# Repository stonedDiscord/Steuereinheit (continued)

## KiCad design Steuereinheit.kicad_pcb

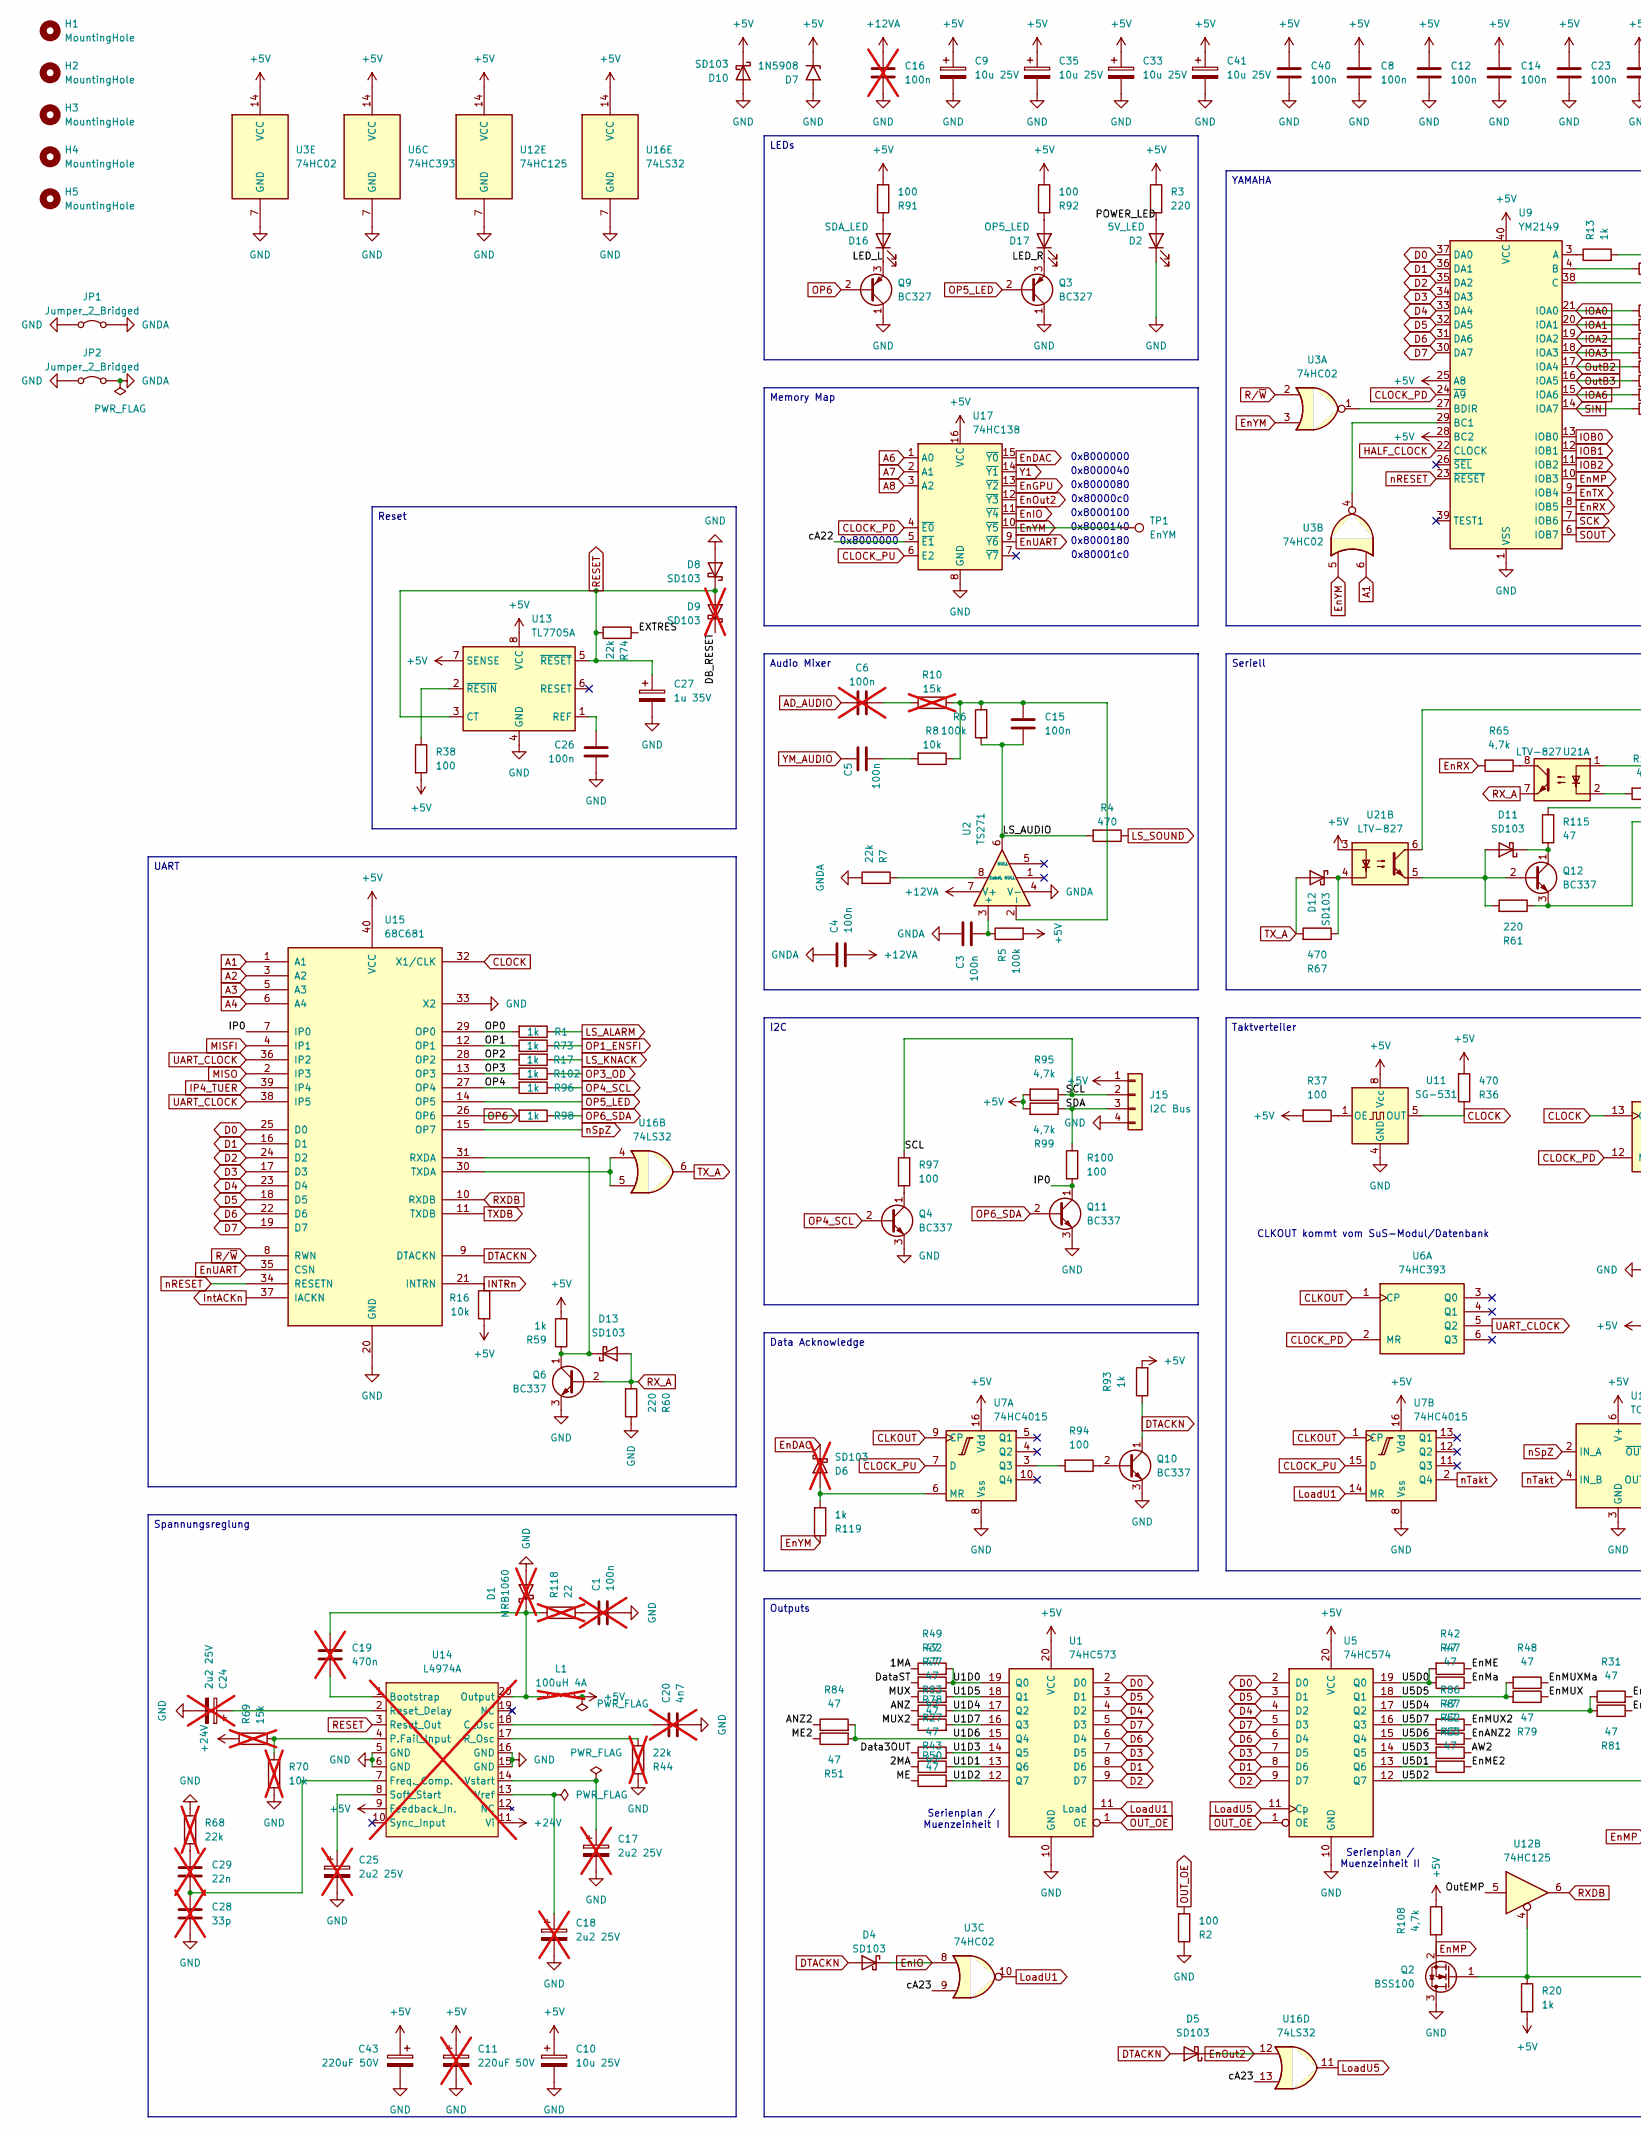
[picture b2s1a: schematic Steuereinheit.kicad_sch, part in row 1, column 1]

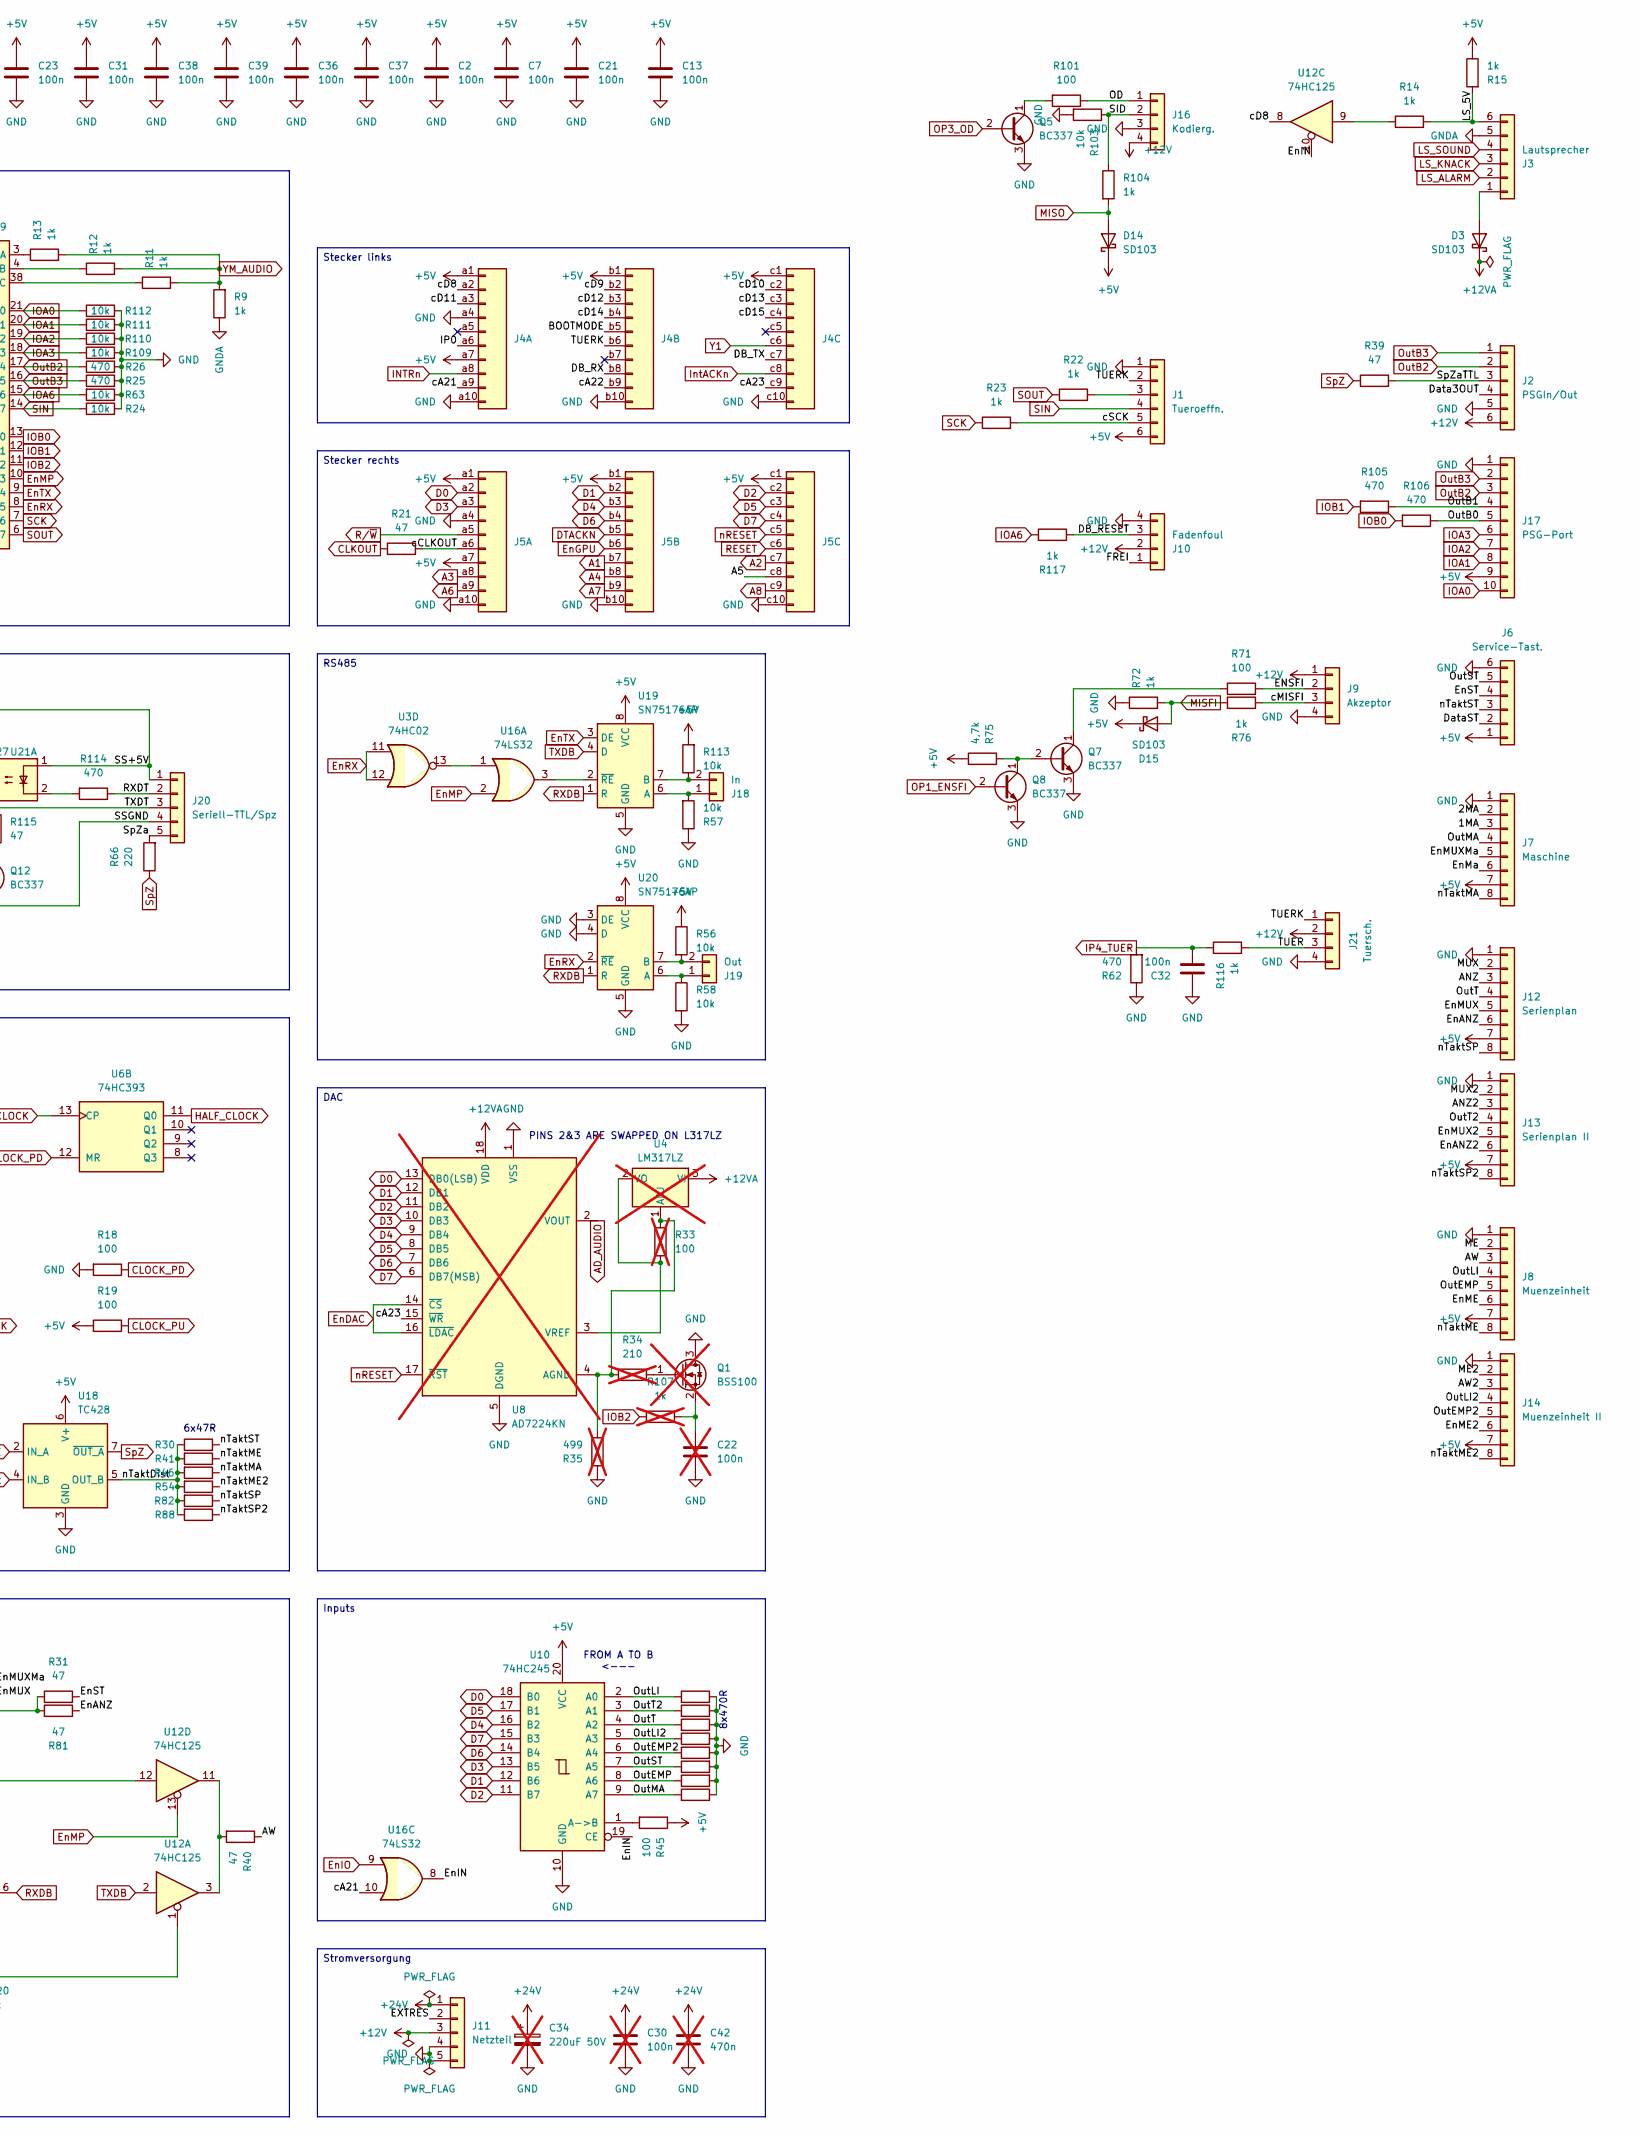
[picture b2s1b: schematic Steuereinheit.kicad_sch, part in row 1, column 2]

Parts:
C1, C6, C16, C22, C30: 100n; C_Axial_L3.8mm_D2.6mm_P7.50mm_Horizontal; not fitted
C2, C3, C4, C5, C7, C8, C12, C13, C14, C15, C21, C23, C26, C31, C32, C36, C37, C38, C39, C40: 100n; C_Axial_L3.8mm_D2.6mm_P7.50mm_Horizontal
C9, C10, C33, C35, C41: 10u 25V; CP_Radial_Tantal_D4.5mm_P2.50mm
C11, C34: 220uF 50V; CP_Radial_D12.5mm_P5.00mm; not fitted
C17, C18, C24, C25: 2u2 25V; CP_Radial_Tantal_D4.5mm_P2.50mm; not fitted
C19, C42: 470n; C_Rect_L9.0mm_W2.5mm_P7.50mm_MKT; not fitted
C20: 4n7; C_Rect_L7.0mm_W2.0mm_P5.00mm; not fitted
C27: 1u 35V; CP_Radial_Tantal_D4.5mm_P2.50mm
C28: 33p; C_Disc_D3.0mm_W1.6mm_P2.50mm; not fitted
C29: 22n; C_Rect_L7.0mm_W2.0mm_P5.00mm; not fitted
C43: 220uF 50V; CP_Radial_D12.5mm_P5.00mm
D1: MRB1060; TO-220-2_Vertical; not fitted
D2: 5V_LED; LED_D5.0mm
D3, D4, D5, D8, D10, D11, D12, D13, D14, D15: SD103; D_DO-35_SOD27_P7.62mm_Horizontal
D6, D9: SD103; D_DO-35_SOD27_P7.62mm_Horizontal; not fitted
D7: 1N5908; D_DO-201AE_P15.24mm_Horizontal
D16: SDA_LED; LED_D5.0mm
D17: OP5_LED; LED_D5.0mm
H1, H2, H3, H4, H5: MountingHole; MountingHole_4.3mm_M4
J1: Tueroeffn.; PinHeader_1x06_P2.54mm_Vertical
J2: PSGIn/Out; PinHeader_1x06_P2.54mm_Vertical
J3: Lautsprecher; PinHeader_1x06_P2.54mm_Vertical
J4, J5: DIN41612_03x10_ABC
J6: Service-Tast.; PinHeader_1x06_P2.54mm_Vertical
J7: Maschine; PinHeader_1x08_P2.54mm_Vertical
J8: Muenzeinheit; PinHeader_1x08_P2.54mm_Vertical
J9: Akzeptor; PinHeader_1x04_P2.54mm_Vertical
J10: Fadenfoul; PinHeader_1x04_P2.54mm_Vertical
J11: Netzteil; PinHeader_1x05_P2.54mm_Vertical
J12: Serienplan; PinHeader_1x08_P2.54mm_Vertical
J13: Serienplan II; PinHeader_1x08_P2.54mm_Vertical
J14: Muenzeinheit II; PinHeader_1x08_P2.54mm_Vertical
J15: I2C Bus; PinHeader_1x04_P2.54mm_Vertical
J16: Kodierg.; PinHeader_1x04_P2.54mm_Vertical
J17: PSG-Port; PinHeader_1x10_P2.54mm_Vertical
J18: In; PinHeader_1x02_P2.54mm_Vertical
J19: Out; PinHeader_1x02_P2.54mm_Vertical
J20: Seriell-TTL/Spz; PinHeader_1x05_P2.54mm_Vertical
J21: Tuersch.; PinHeader_1x04_P2.54mm_Vertical
JP1, JP2: Jumper_2_Bridged; SolderJumper-2_P1.3mm_Bridged_Pad1.0x1.5mm
L1: 100uH 4A; L_Toroid_Vertical_L24.6mm_W15.5mm_P11.44mm_Pulse_KM-4; not fitted
Q1: BSS100; TO-92; not fitted
Q2: BSS100; TO-92
Q3, Q9: BC327; TO-92
Q4, Q5, Q6, Q7, Q8, Q10, Q11, Q12: BC337; TO-92
R1, R9, R11, R12, R13, R14, R15, R17, R20, R22, R23, R59, R72, R73, R76, R93, R96, R98, R102, R104, R116, R117, R119: 1k; R_Axial_DIN0207_L6.3mm_D2.5mm_P10.16mm_Horizontal
R2, R18, R19, R37, R38, R45, R71, R91, R92, R94, R97, R100, R101: 100; R_Axial_DIN0207_L6.3mm_D2.5mm_P10.16mm_Horizontal
R3, R60, R61, R66: 220; R_Axial_DIN0207_L6.3mm_D2.5mm_P10.16mm_Horizontal
R4, R25, R26, R28, R29, R36, R55, R62, R64, R67, R80, R85, R89, R90, R105, R106, R114: 470; R_Axial_DIN0207_L6.3mm_D2.5mm_P10.16mm_Horizontal
R5, R6: 100k; R_Axial_DIN0207_L6.3mm_D2.5mm_P10.16mm_Horizontal
R7, R74: 22k; R_Axial_DIN0207_L6.3mm_D2.5mm_P10.16mm_Horizontal
R8, R16, R24, R56, R57, R58, R63, R103, R109, R110, R111, R112, R113: 10k; R_Axial_DIN0207_L6.3mm_D2.5mm_P10.16mm_Horizontal
R10, R69: 15k; R_Axial_DIN0207_L6.3mm_D2.5mm_P10.16mm_Horizontal; not fitted
R21, R27, R30, R31, R32, R39, R40, R41, R42, R43, R46, R47, R48, R49, R50, R51, R52, R53, R54, R77, R78, R79, R81, R82, R83, R84, R86, R87, R88, R115: 47; R_Axial_DIN0207_L6.3mm_D2.5mm_P10.16mm_Horizontal
R33: 100; R_Axial_DIN0207_L6.3mm_D2.5mm_P10.16mm_Horizontal; not fitted
R34: 210; R_Axial_DIN0207_L6.3mm_D2.5mm_P10.16mm_Horizontal; not fitted
R35: 499; R_Axial_DIN0207_L6.3mm_D2.5mm_P10.16mm_Horizontal; not fitted
R44, R68: 22k; R_Axial_DIN0207_L6.3mm_D2.5mm_P10.16mm_Horizontal; not fitted
R65, R75, R95, R99, R108: 4,7k; R_Axial_DIN0207_L6.3mm_D2.5mm_P10.16mm_Horizontal
R70: 10k; R_Axial_DIN0207_L6.3mm_D2.5mm_P10.16mm_Horizontal; not fitted
R107: 1k; R_Axial_DIN0207_L6.3mm_D2.5mm_P10.16mm_Horizontal; not fitted
R118: 22; R_Axial_DIN0207_L6.3mm_D2.5mm_P10.16mm_Horizontal; not fitted
TP1: EnYM; TestPoint_Pad_D1.0mm
U1: 74HC573; DIP-20_W7.62mm
U2: TS271; DIP-8_W7.62mm
U3: 74HC02; DIP-14_W7.62mm
U4: LM317LZ; TO-92; not fitted
U5: 74HC574; DIP-20_W7.62mm
U6: 74HC393; DIP-14_W7.62mm
U7: 74HC4015; DIP-16_W7.62mm
U8: AD7224KN; DIP-18_W7.62mm; not fitted
U9: YM2149; DIP-40_W15.24mm
U10: 74HC245; DIP-20_W7.62mm
U11: SG-531; Oscillator_SeikoEpson_SG-8002DC
U12: 74HC125; DIP-14_W7.62mm
U13: TL7705A; DIP-8_W7.62mm
U14: L4974A; DIP-20_W7.62mm; not fitted
U15: 68C681; DIP-40_W15.24mm
U16: 74LS32; DIP-14_W7.62mm
U17: 74HC138; DIP-16_W7.62mm
U18: TC428; DIP-8_W7.62mm
U19, U20: SN75176AP; DIP-8_W7.62mm
U21: LTV-827; DIP-8_W7.62mm

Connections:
+5V: C2.2, C7.2, C8.1, C9.1, C10.1, C11.1, C12.1, C13.1, C14.1, C21.1, C23.1, C31.1, C33.1, C35.1, C36.1, C37.1, C38.1, C39.1, C40.1, C41.1, C43.1, D7.1 (A1), D10.1 (K), D14.1 (K), D15.1 (K), J1.6, J4.a1, J4.a7, J4.b1, J4.c1, J5.a1, J5.a7, J5.b1, J5.c1, J6.1, J7.7, J8.7, J12.7, J13.7, J14.7, J15.1, J17.9, L1.2, R3.1, R5.2, R15.1, R16.2, R19.2, R20.2, R36.2, R37.2, R38.2, R45.1, R56.1, R59.2, R75.2, R91.2, R92.2, R93.2, R95.2, R99.2, R108.1, R113.2, U1.20 (VCC), U3.14 (VCC), U5.20 (VCC), U6.14 (VCC), U7.16 (Vdd), U9.25 (A8), U9.28 (BC2), U9.40 (VCC), U10.20 (VCC), U11.8 (Vcc), U12.14 (VCC), U13.7 (SENSE), U13.8 (VCC), U14.9 (Feedback_In.), U15.40 (VCC), U16.14 (VCC), U17.16 (VCC), U18.6 (V+), U19.8 (VCC), U20.8 (VCC), U21.3
+12V: J2.6, J9.1, J10.2, J11.3, J16.4, J21.2
+12VA: C4.2, C16.1, D3.1 (K), U2.7 (V+), U4.3 (VI), U8.18 (VDD)
+24V: C30.1, C34.1, C42.2, J11.1, R69.1, U14.11 (Vi)
/1MA: J7.3, R49.1
/2MA: J7.2, R50.1
/A5: J5.c8
/ANZ: J12.3, R78.1
/ANZ2: J13.3, R84.1
/AW: J8.3, R40.1
/AW2: J14.3, R52.1
/BOOTMODE: J4.b5
/DB_RESET: D9.1 (K), J10.3, R117.1
/DB_RX: J4.b8
/DB_TX: J4.c7
/Data3OUT: J2.4, R27.1
/DataST: J6.2, R32.2
/ENSFI: J9.2, R71.2
/EXTRES: J11.2, R74.1
/EnANZ: J12.6, R81.1
/EnANZ2: J13.6, R87.1
/EnIN: U10.19 (CE), U12.10, U16.8
/EnME: J8.6, R42.1
/EnME2: J14.6, R53.1
/EnMUX: J12.5, R79.1
/EnMUX2: J13.5, R86.1
/EnMUXMa: J7.5, R48.1
/EnMa: J7.6, R47.1
/EnST: J6.4, R31.2
/FREI: J10.1
/IP0: J4.a6, Q11.1 (C), R100.2, U15.7 (IP0)
/LED_L: D16.1 (K), Q9.3 (E)
/LED_R: D17.1 (K), Q3.3 (E)
/LS_5V: J3.6, R14.2, R15.2
/LS_AUDIO: C15.2, R4.2, R6.2, U2.6
/ME: J8.2, R43.1
/ME2: J14.2, R51.1
/MUX: J12.2, R77.1
/MUX2: J13.2, R83.1
/OD: J16.1, R101.1
/OP0: R1.2, U15.29 (OP0)
/OP1: R73.2, U15.12 (OP1)
/OP2: R17.1, U15.28 (OP2)
/OP3: R102.2, U15.13 (OP3)
/OP4: R96.2, U15.27 (OP4)
/OutB0: J17.5, R106.1
/OutB1: J17.4, R105.1
/OutEMP: J8.5, R29.1, U10.8 (A6), U12.5
/OutEMP2: J14.5, R90.1, U10.6 (A4)
/OutLI: J8.4, R64.2, U10.2 (A0)
/OutLI2: J14.4, R89.1, U10.5 (A3)
/OutMA: J7.4, R55.2, U10.9 (A7)
/OutST: J6.5, R28.1, U10.7 (A5)
/OutT: J12.4, R80.2, U10.4 (A2)
/OutT2: J13.4, R85.2, U10.3 (A1)
/POWER_LED: D2.2 (A), R3.2
/RXDT: J20.2, R114.1
/SCL: J15.2, R95.1, R97.1
/SDA: J15.3, R99.1, R100.1
/SID: J16.2, R103.1, R104.1
/SS+5V: J20.1, U21.1, U21.6
/SSGND: J20.4, Q12.3 (E), R61.1
/SpZa: J20.5, R66.2
/SpZaTTL: J2.3, R39.2
/TUER: J21.3, R116.1
/TUERK: J1.2, J4.b6, J21.1
/TXDT: J20.3, R115.1
/U1D0: R32.1, R49.2, U1.19 (Q0)
/U1D1: R50.2, U1.13 (Q6)
/U1D2: R43.2, U1.12 (Q7)
/U1D3: R27.2, U1.14 (Q5)
/U1D4: R78.2, U1.17 (Q2)
/U1D5: R77.2, U1.18 (Q1)
/U1D6: R51.2, R84.2, U1.15 (Q4)
/U1D7: R83.2, U1.16 (Q3)
/U5D0: R42.2, R47.2, U5.19 (Q0)
/U5D1: R53.2, U5.13 (Q6)
/U5D2: U5.12 (Q7), U12.12
/U5D3: R52.2, U5.14 (Q5)
/U5D4: R31.1, R81.2, U5.17 (Q2)
/U5D5: R48.2, R79.2, U5.18 (Q1)
/U5D6: R87.2, U5.15 (Q4)
/U5D7: R86.2, U5.16 (Q3)
/cA21: J4.a9, U16.10
/cA22: J4.b9, U17.5 (~E1)
/cA23: J4.c9, U3.9, U8.15 (~WR), U16.13
/cCLKOUT: J5.a6, R21.2
/cD8: J4.a2, U12.8
/cD9: J4.b2
/cD10: J4.c2
/cD11: J4.a3
/cD12: J4.b3
/cD13: J4.c3
/cD14: J4.b4
/cD15: J4.c4
/cMISFI: J9.3, R76.1
/cSCK: J1.5, R23.2
/nTaktDist: R30.1, R41.2, R46.2, R54.2, R82.2, R88.2, U18.5 (OUT_B)
/nTaktMA: J7.8, R46.1
/nTaktME: J8.8, R41.1
/nTaktME2: J14.8, R54.1
/nTaktSP: J12.8, R82.1
/nTaktSP2: J13.8, R88.1
/nTaktST: J6.3, R30.2
A1: J5.b7, U3.6, U15.1 (A1)
A2: J5.c7, U15.3 (A2)
A3: J5.a8, U15.5 (A3)
A4: J5.b8, U15.6 (A4)
A6: J5.a9, U17.1 (A0)
A7: J5.b9, U17.2 (A1)
A8: J5.c9, U17.3 (A2)
AD_AUDIO: C6.1, U8.2 (VOUT)
CLKOUT: R21.1, U6.1 (CP), U7.1 (CP), U7.9 (CP)
CLOCK: R36.1, U6.13 (CP), U11.5 (OUT), U15.32 (X1/CLK)
CLOCK_PD: R18.1, U6.2 (MR), U6.12 (MR), U9.24 (~A9), U17.4 (~E0)
CLOCK_PU: R19.1, U7.7 (D), U7.15 (D), U17.6 (E2)
D0: J5.a2, U1.2 (D0), U5.2 (D0), U8.13 (DB0(LSB)), U9.37 (DA0), U10.18 (B0), U15.25 (D0)
D1: J5.b2, U1.8 (D6), U5.8 (D6), U8.12 (DB1), U9.36 (DA1), U10.12 (B6), U15.16 (D1)
D2: J5.c2, U1.9 (D7), U5.9 (D7), U8.11 (DB2), U9.35 (DA2), U10.11 (B7), U15.24 (D2)
D3: J5.a3, U1.7 (D5), U5.7 (D5), U8.10 (DB3), U9.34 (DA3), U10.13 (B5), U15.17 (D3)
D4: J5.b3, U1.4 (D2), U5.4 (D2), U8.9 (DB4), U9.33 (DA4), U10.16 (B2), U15.23 (D4)
D5: J5.c3, U1.3 (D1), U5.3 (D1), U8.8 (DB5), U9.32 (DA5), U10.17 (B1), U15.18 (D5)
D6: J5.b4, U1.6 (D4), U5.6 (D4), U8.7 (DB6), U9.31 (DA6), U10.14 (B4), U15.22 (D6)
D7: J5.c4, U1.5 (D3), U5.5 (D3), U8.6 (DB7(MSB)), U9.30 (DA7), U10.15 (B3), U15.19 (D7)
DTACKN: D4.2 (A), D5.2 (A), J5.b5, Q10.1 (C), R93.1, U15.9 (DTACKN)
EnDAC: D6.1 (K), U8.14 (~CS), U8.16 (~LDAC), U17.15 (~Y0)
EnGPU: J5.b6, U17.13 (~Y2)
EnIO: D4.1 (K), U3.8, U16.9, U17.11 (~Y4)
EnMP: Q2.2 (S), R108.2, U9.10 (IOB3), U12.13, U16.2
EnOut2: D5.1 (K), U16.12, U17.12 (~Y3)
EnRX: R65.2, U3.11, U3.12, U9.8 (IOB5), U20.2 (~RE)
EnTX: U9.9 (IOB4), U19.3 (DE)
EnUART: U15.35 (CSN), U17.9 (~Y6)
EnYM: R119.1, TP1.1, U3.3, U3.5, U17.10 (~Y5)
GND: C1.2, C2.1, C7.1, C8.2, C9.2, C10.2, C11.2, C12.2, C13.2, C14.2, C16.2, C17.2, C18.2, C20.1, C21.2, C22.2, C23.2, C24.2, C25.2, C26.2, C27.2, C28.2, C30.2, C31.2, C32.1, C33.2, C34.2, C35.2, C36.2, C37.2, C38.2, C39.2, C40.2, C41.2, C42.1, C43.2, D1.2 (A), D2.1 (K), D7.2 (A2), D8.2 (A), D10.2 (A), J1.1, J2.5, J4.a4, J4.a10, J4.b10, J4.c10, J5.a4, J5.a10, J5.b10, J5.c10, J6.6, J7.1, J8.1, J9.4, J10.4, J11.4, J11.5, J12.1, J13.1, J14.1, J15.4, J16.3, J17.1, J21.4, JP1.1 (A), JP2.1 (A), Q1.3 (D), Q2.3 (D), Q3.1 (C), Q4.3 (E), Q5.3 (E), Q6.3 (E), Q7.3 (E), Q8.3 (E), Q9.1 (C), Q10.3 (E), Q11.3 (E), R2.1, R18.2, R24.2, R25.2, R26.2, R28.2, R29.2, R35.1, R44.1, R55.1, R57.1, R58.2, R60.1, R62.1, R63.1, R64.1, R68.1, R70.1, R72.1, R80.1, R85.1, R89.2, R90.2, R103.2, R109.2, R110.2, R111.2, R112.2, U1.10 (GND), U3.7 (GND), U5.10 (GND), U6.7 (GND), U7.8 (Vss), U8.1 (VSS), U8.5 (DGND), U9.1 (VSS), U10.10 (GND), U11.4 (GND), U12.7 (GND), U13.4 (GND), U14.5 (GND), U14.6 (GND), U14.15 (GND), U14.16 (GND), U15.20 (GND), U15.33 (X2), U16.7 (GND), U17.8 (GND), U18.3 (GND), U19.5 (GND), U20.3 (DE), U20.4 (D), U20.5 (GND)
GNDA: C3.2, C4.1, J3.5, JP1.2 (B), JP2.2 (B), R7.2, R9.1, U2.4 (V-)
HALF_CLOCK: U6.11 (Q0), U9.22 (CLOCK)
INTRN: J4.a8, R16.1, U15.21 (INTRN)
IOA0: J17.10, R112.1, U9.21 (IOA0)
IOA1: J17.8, R111.1, U9.20 (IOA1)
IOA2: J17.7, R110.1, U9.19 (IOA2)
IOA3: J17.6, R109.1, U9.18 (IOA3)
IOA6: R63.2, R117.2, U9.15 (IOA6)
IOB0: R106.2, U9.13 (IOB0)
IOB1: R105.2, U9.12 (IOB1)
IOB2: R107.2, U9.11 (IOB2)
IP4_TUER: C32.2, R62.2, R116.2, U15.39 (IP4)
IntACKn: J4.c8, U15.37 (IACKN)
LS_ALARM: J3.2, R1.1
LS_KNACK: J3.3, R17.2
LS_SOUND: J3.4, R4.1
LoadU1: U1.11 (Load), U3.10, U7.14 (MR)
LoadU5: U5.11 (Cp), U16.11
MISFI: D15.2 (A), R72.2, R76.2, U15.4 (IP1)
MISO: D14.2 (A), R104.2, U15.2 (IP3)
unnamed: C1.1, R118.1
unnamed: C5.2, R8.2
unnamed: C6.2, R10.2
unnamed: C29.1, R68.2
unnamed: C19.2, D1.1 (K), L1.1, R118.2, U14.20 (Output)
unnamed: D3.2 (A), J3.1
unnamed: D6.2 (A), R119.2, U7.6 (MR)
unnamed: D11.2 (A), Q12.2 (B), R61.2, U21.5
unnamed: D11.1 (K), Q12.1 (C), R115.2
unnamed: D12.1 (K), R67.1, U21.4
unnamed: D13.1 (K), Q6.1 (C), R59.1, U15.31 (RXDA)
unnamed: D16.2 (A), R91.1
unnamed: D17.2 (A), R92.1
unnamed: J1.3, R22.2
unnamed: J18.1, R57.2, U19.6 (A)
unnamed: J18.2, R113.1, U19.7 (B)
unnamed: J19.1, R58.1, U20.6 (A)
unnamed: J19.2, R56.2, U20.7 (B)
unnamed: Q1.1 (G), R34.1
unnamed: C22.1, Q1.2 (S), R107.1
unnamed: Q2.1 (G), R20.1, U12.1, U12.4
unnamed: Q4.1 (C), R97.2
unnamed: Q5.1 (C), R101.2
unnamed: Q7.2 (B), Q8.1 (C), R75.1
unnamed: Q7.1 (C), R71.1
unnamed: Q10.2 (B), R94.1
unnamed: R14.1, U12.9
unnamed: R40.2, U12.3, U12.11
unnamed: R65.1, U21.8
unnamed: R114.2, U21.2
unnamed: C3.1, R5.1, U2.3 (+)
unnamed: C15.1, R6.1, R8.1, R10.1, U2.2 (-)
unnamed: R7.1, U2.8 (Subst.)
unnamed: R33.2, R34.2, R35.2, U4.1 (ADJ), U8.4 (AGND)
unnamed: R33.1, U4.2 (VO), U8.3 (VREF)
unnamed: R94.2, U7.3 (Q3)
unnamed: R13.1, U9.3 (A)
unnamed: R12.1, U9.4 (B)
unnamed: U3.4, U9.29 (BC1)
unnamed: U3.1, U9.27 (BDIR)
unnamed: R11.1, U9.38 (C)
unnamed: R45.2, U10.1 (A->B)
unnamed: R37.1, U11.1 (OE)
unnamed: C26.1, U13.1 (REF)
unnamed: R38.1, U13.2 (~RESIN)
unnamed: C19.1, U14.1 (Bootstrap)
unnamed: C20.2, U14.18 (C_Osc)
unnamed: C28.1, C29.2, U14.7 (Freq._Comp.)
unnamed: R69.2, R70.2, U14.4 (P.Fail_Input)
unnamed: R44.2, U14.17 (R_Osc)
unnamed: C24.1, U14.2 (Reset_Delay)
unnamed: C25.1, U14.8 (Soft_Start)
unnamed: C18.1, U14.13 (Vref)
unnamed: C17.1, U14.14 (Vstart)
unnamed: U15.30 (TXDA), U16.4, U16.5
unnamed: U3.13, U16.1
unnamed: U16.3, U19.2 (~RE)
OP1_ENSFI: Q8.2 (B), R73.1
OP3_OD: Q5.2 (B), R102.1
OP4_SCL: Q4.2 (B), R96.1
OP5_LED: Q3.2 (B), U15.14 (OP5)
OP6: Q9.2 (B), R98.2, U15.26 (OP6)
OP6_SDA: Q11.2 (B), R98.1
OUT_OE: R2.2, U1.1 (OE), U5.1 (OE)
OutB2: J2.2, J17.3, R26.1, U9.17 (IOA4)
OutB3: J2.1, J17.2, R25.1, U9.16 (IOA5)
RESET: C27.1, D8.1 (K), D9.2 (A), J5.c6, R74.2, U13.3 (CT), U13.5 (~RESET), U14.3 (Reset_Out)
RXDB: U12.6, U15.10 (RXDB), U19.1 (R), U20.1 (R)
RX_A: D13.2 (A), Q6.2 (B), R60.2, U21.7
R/~W: J5.a5, U3.2, U15.8 (RWN)
SCK: R23.1, U9.7 (IOB6)
SIN: J1.4, R24.1, U9.14 (IOA7)
SOUT: R22.1, U9.6 (IOB7)
SpZ: R39.1, R66.1, U18.7 (~OUT_A)
TXDB: U12.2, U15.11 (TXDB), U19.4 (D)
TX_A: D12.2 (A), R67.2, U16.6
UART_CLOCK: U6.5 (Q2), U15.36 (IP2), U15.38 (IP5)
Y1: J4.c6, U17.14 (~Y1)
YM_AUDIO: C5.1, R9.2, R11.2, R12.2, R13.2
nRESET: J5.c5, U8.17 (~RST), U9.23 (~RESET), U15.34 (RESETN)
nSpZ: U15.15 (OP7), U18.2 (IN_A)
nTakt: U7.2 (Q4), U18.4 (IN_B)

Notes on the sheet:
0x8000100
Serienplan / Muenzeinheit II
0x8000180
PINS 2&3 ARE SWAPPED ON L317LZ
6x47R
0x8000000
8x470R
Serienplan / Muenzeinheit I
0x8000080
0x80001c0
0x8000140
0x8000040
FROM A TO B <---
0x80000c0
CLKOUT kommt vom SuS-Modul/Datenbank
Seriell
UART
DAC
I2C
Stecker links
LEDs
Inputs
Audio Mixer
Memory Map
Taktverteiler
Stromversorgung
RS485
Stecker rechts
Outputs
Data Acknowledge
Reset
YAMAHA
Spannungsreglung

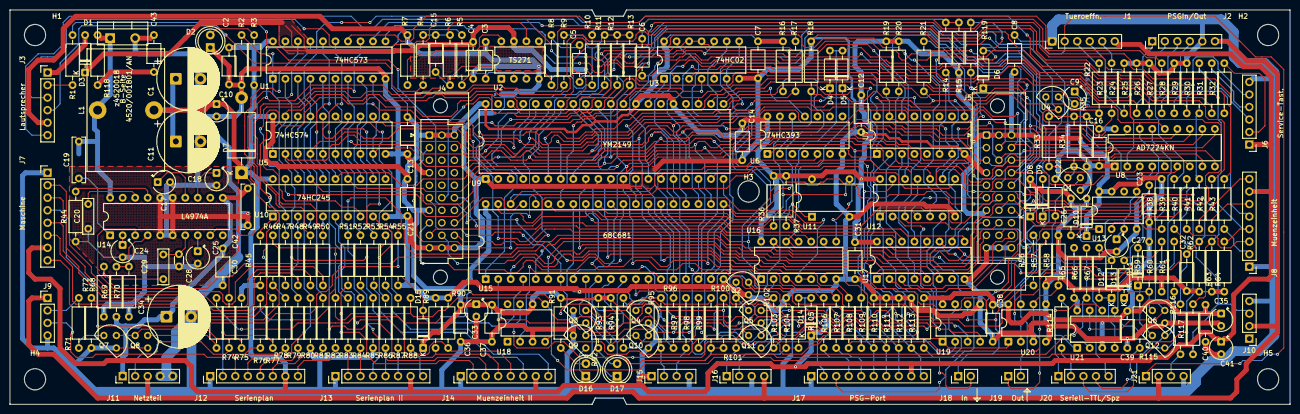
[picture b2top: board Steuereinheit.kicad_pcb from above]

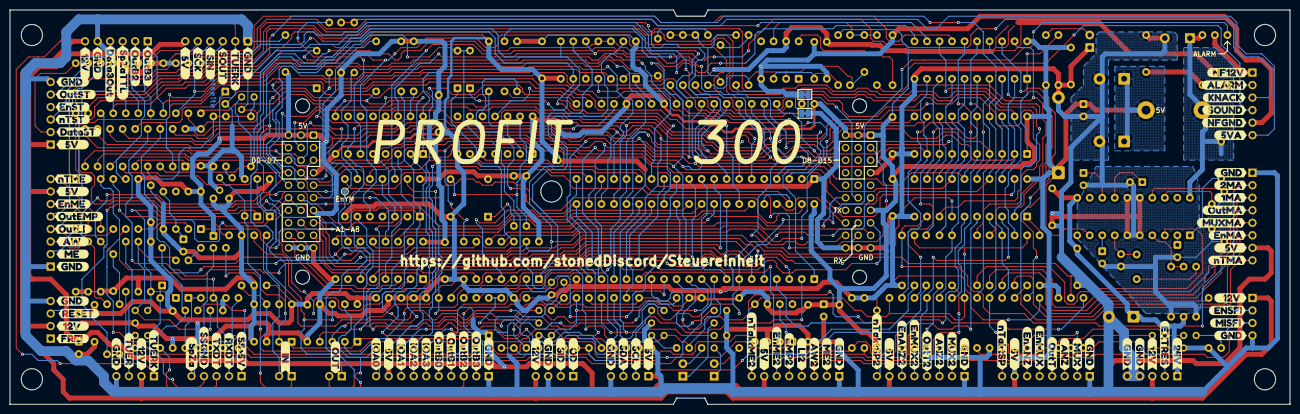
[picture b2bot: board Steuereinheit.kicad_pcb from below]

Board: 2 copper layers, 259.7 x 80.0 mm, 348 parts (109 on the bottom side), 225 nets.

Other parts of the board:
kibuzzard-6872A0A4: G***; kibuzzard-6872A0A4
kibuzzard-6872A0AF: G***; kibuzzard-6872A0AF
kibuzzard-6872A0B8: G***; kibuzzard-6872A0B8
kibuzzard-6872A0D0: G***; kibuzzard-6872A0D0
kibuzzard-6872A1B2: G***; kibuzzard-6872A1B2
kibuzzard-6872A1BE: G***; kibuzzard-6872A1BE
kibuzzard-6872A1D7: G***; kibuzzard-6872A1D7
kibuzzard-6872A1DE: G***; kibuzzard-6872A1DE
kibuzzard-6872A1E6: G***; kibuzzard-6872A1E6
kibuzzard-6872A1ED: G***; kibuzzard-6872A1ED
kibuzzard-6872A1F5: G***; kibuzzard-6872A1F5
kibuzzard-6872A2D1: G***; kibuzzard-6872A2D1
kibuzzard-6872A3BA: G***; kibuzzard-6872A3BA
kibuzzard-6872A3CC: G***; kibuzzard-6872A3CC
kibuzzard-6872A4A7: G***; kibuzzard-6872A4A7
kibuzzard-6872A4B2: G***; kibuzzard-6872A4B2
kibuzzard-6872A4BB: G***; kibuzzard-6872A4BB
kibuzzard-6872A4C0: G***; kibuzzard-6872A4C0
kibuzzard-6872A4C7: G***; kibuzzard-6872A4C7
kibuzzard-6872A4D0: G***; kibuzzard-6872A4D0
kibuzzard-6872A4D7: G***; kibuzzard-6872A4D7
kibuzzard-6872A04E: G***; kibuzzard-6872A04E
kibuzzard-6872A4E7, kibuzzard-6872A4E7#2: G***; kibuzzard-6872A4E7
kibuzzard-6872A4F2: G***; kibuzzard-6872A4F2
kibuzzard-6872A4FD: G***; kibuzzard-6872A4FD
kibuzzard-6872A5D0: G***; kibuzzard-6872A5D0
kibuzzard-6872A5D9: G***; kibuzzard-6872A5D9
kibuzzard-6872A5E5: G***; kibuzzard-6872A5E5
kibuzzard-6872A06E: G***; kibuzzard-6872A06E
kibuzzard-6872A12C: G***; kibuzzard-6872A12C
kibuzzard-6872A15D: G***; kibuzzard-6872A15D
kibuzzard-6872A18D: G***; kibuzzard-6872A18D
kibuzzard-6872A19B: G***; kibuzzard-6872A19B
kibuzzard-6872A19E: G***; kibuzzard-6872A19E
kibuzzard-6872A21C: G***; kibuzzard-6872A21C
kibuzzard-6872A24B: G***; kibuzzard-6872A24B
kibuzzard-6872A33C: G***; kibuzzard-6872A33C
kibuzzard-6872A37B: G***; kibuzzard-6872A37B
kibuzzard-6872A041: G***; kibuzzard-6872A041
kibuzzard-6872A45D: G***; kibuzzard-6872A45D
kibuzzard-6872A46F: G***; kibuzzard-6872A46F
kibuzzard-6872A49D: G***; kibuzzard-6872A49D
kibuzzard-6872A50A: G***; kibuzzard-6872A50A
kibuzzard-6872A52D: G***; kibuzzard-6872A52D
kibuzzard-6872A53B: G***; kibuzzard-6872A53B
kibuzzard-6872A55F: G***; kibuzzard-6872A55F
kibuzzard-6872A065: G***; kibuzzard-6872A065
kibuzzard-6872A088: G***; kibuzzard-6872A088
kibuzzard-6872A091: G***; kibuzzard-6872A091
kibuzzard-6872A099: G***; kibuzzard-6872A099
kibuzzard-6872A111: G***; kibuzzard-6872A111
kibuzzard-6872A119: G***; kibuzzard-6872A119
kibuzzard-6872A123: G***; kibuzzard-6872A123
kibuzzard-6872A136: G***; kibuzzard-6872A136
kibuzzard-6872A144, kibuzzard-6872A144#2: G***; kibuzzard-6872A144
kibuzzard-6872A155: G***; kibuzzard-6872A155
kibuzzard-6872A209: G***; kibuzzard-6872A209
kibuzzard-6872A215: G***; kibuzzard-6872A215
kibuzzard-6872A252: G***; kibuzzard-6872A252
kibuzzard-6872A278: G***; kibuzzard-6872A278
kibuzzard-6872A280: G***; kibuzzard-6872A280
kibuzzard-6872A286: G***; kibuzzard-6872A286
kibuzzard-6872A326: G***; kibuzzard-6872A326
kibuzzard-6872A337: G***; kibuzzard-6872A337
kibuzzard-6872A344: G***; kibuzzard-6872A344
kibuzzard-6872A368: G***; kibuzzard-6872A368
kibuzzard-6872A375: G***; kibuzzard-6872A375
kibuzzard-6872A380: G***; kibuzzard-6872A380
kibuzzard-6872A444: G***; kibuzzard-6872A444
kibuzzard-6872A450: G***; kibuzzard-6872A450
kibuzzard-6872A456: G***; kibuzzard-6872A456
kibuzzard-6872A466: G***; kibuzzard-6872A466
kibuzzard-6872A486: G***; kibuzzard-6872A486
kibuzzard-6872A510: G***; kibuzzard-6872A510
kibuzzard-6872A519: G***; kibuzzard-6872A519
kibuzzard-6872A545: G***; kibuzzard-6872A545
kibuzzard-6872A554: G***; kibuzzard-6872A554
kibuzzard-6872A576: G***; kibuzzard-6872A576
kibuzzard-6872A580: G***; kibuzzard-6872A580
kibuzzard-68729E03, kibuzzard-68729E03#2, kibuzzard-68729E03#3, kibuzzard-68729E03#4, kibuzzard-68729E03#5: G***; kibuzzard-68729E03
kibuzzard-68729E6A, kibuzzard-68729E6A#2: G***; kibuzzard-68729E6A
kibuzzard-68729E7B: G***; kibuzzard-68729E7B
kibuzzard-68729E8F, kibuzzard-68729E8F#2, kibuzzard-68729E8F#3, kibuzzard-68729E8F#4: G***; kibuzzard-68729E8F
kibuzzard-68729F15, kibuzzard-68729F15#2, kibuzzard-68729F15#3, kibuzzard-68729F15#4, kibuzzard-68729F15#5, kibuzzard-68729F15#6, kibuzzard-68729F15#7: G***; kibuzzard-68729F15
kibuzzard-68729F75, kibuzzard-68729F75#2: G***; kibuzzard-68729F75
kibuzzard-68729FCB: G***; kibuzzard-68729FCB
kibuzzard-68729FE2: G***; kibuzzard-68729FE2
kibuzzard-68729FEA: G***; kibuzzard-68729FEA
kibuzzard-68729FF2: G***; kibuzzard-68729FF2

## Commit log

2025-03-26 leiterbahnen
2025-03-26 widers
2025-03-26 widerstand
2025-03-27 serial
2025-03-27 alle bauteile
2025-03-27 unterseite
2025-03-27 power
2025-04-14 data
2025-04-15 vorne
2025-04-16 widerstände reihenfolge
2025-05-02 linguist override
2025-06-10 serienplan
2025-06-19 vorderseite und verdrahtungsplan
2025-06-20 fertig?
2025-06-20 op pins
2025-06-29 notes
2025-07-09 suqash old
2025-07-09 no scan
2025-07-09 noch mehr cleanup
2025-07-09 gitignore
2025-07-11 ntakt chip
2025-07-12 label
2025-11-02 bootmode
2025-12-15 mixer
2026-02-15 lampen
2026-03-07 serienplan2
2026-03-31 anzeigen
2026-03-31 dnp 12v
2026-03-31 sp board outline
2026-03-31 size mosfet
